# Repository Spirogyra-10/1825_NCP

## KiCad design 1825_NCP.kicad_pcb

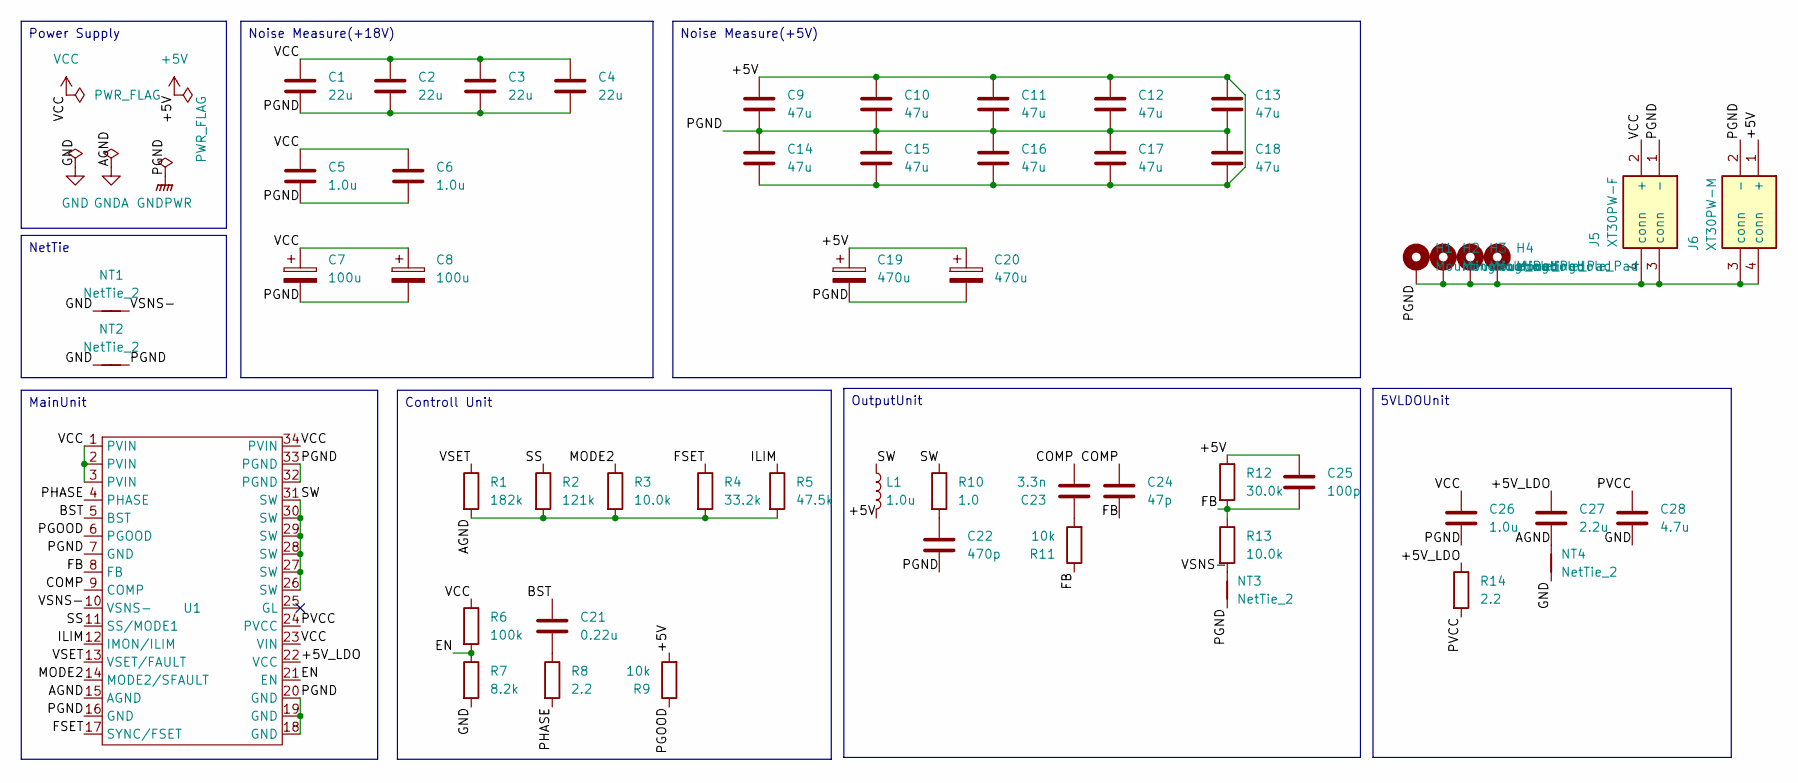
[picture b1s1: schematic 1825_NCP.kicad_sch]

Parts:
C1, C2, C3, C4: 22u; C_1210_3225Metric
C5, C6: 1.0u; C_0603_1608Metric
C7, C8: 100u; CP_Elec_8x10
C9, C10, C11, C12, C13, C14, C15, C16, C17, C18: 47u; C_1206_3216Metric
C19, C20: 470u; CP_EIA-7343-31_Kemet-D
C21: 0.22u; C_0603_1608Metric
C22: 470p; C_0805_2012Metric
C23: 3.3n; C_0603_1608Metric
C24: 47p; C_0603_1608Metric
C25: 100p; C_0603_1608Metric
C26: 1.0u; C_0805_2012Metric
C27: 2.2u; C_0603_1608Metric
C28: 4.7u; C_0805_2012Metric
H1, H2, H3, H4: MountingHole_Pad; MountingHole_3.2mm_M3_Pad_Via
J5: XT30PW-F; XT30PWF; Manufacturer_Part_Number XT30PW-F
J6: XT30PW-M; XT30PWM; Manufacturer_Part_Number XT30PW-M
L1: 1.0u; Pulse_PA4343
NT1, NT2, NT3, NT4: NetTie_2; NetTie-2_SMD_Pad0.5mm
R1: 182k; R_0603_1608Metric
R2: 121k; R_0603_1608Metric
R3, R13: 10.0k; R_0603_1608Metric
R4: 33.2k; R_0603_1608Metric
R5: 47.5k; R_0603_1608Metric
R6: 100k; R_0603_1608Metric
R7: 8.2k; R_0603_1608Metric
R8, R14: 2.2; R_0603_1608Metric
R9, R11: 10k; R_0603_1608Metric
R10: 1.0; R_1206_3216Metric
R12: 30.0k; R_0603_1608Metric
U1: NCP3294

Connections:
+5V: C9.1, C10.1, C11.1, C12.1, C13.1, C14.2, C15.2, C16.2, C17.2, C18.2, C19.1, C20.1, C25.1, J6.1 (+), L1.2, R9.2, R12.1
/+5V_LDO: C27.1, R14.1, U1.22 (VCC)
/BST: C21.1, U1.5 (BST)
/COMP: C23.2, C24.1, U1.9 (COMP)
/EN: R6.2, R7.1, U1.21 (EN)
/FB: C24.2, C25.2, R11.1, R12.2, R13.1, U1.8 (FB)
/FSET: R4.1, U1.17 (SYNC/FSET)
/ILIM: R5.1, U1.12 (IMON/ILIM)
/MODE2: R3.1, U1.14 (MODE2/SFAULT)
/PGOOD: R9.1, U1.6 (PGOOD)
/PHASE: R8.2, U1.4 (PHASE)
/PVCC: C28.1, R14.2, U1.24 (PVCC)
/SS: R2.1, U1.11 (SS/MODE1)
/SW: L1.1, R10.1, U1.26 (SW), U1.27 (SW), U1.28 (SW), U1.29 (SW), U1.30 (SW), U1.31 (SW)
/VSET: R1.1, U1.13 (VSET/FAULT)
/VSNS-: NT1.2, NT3.2, R13.2, U1.10 (VSNS-)
GND: C28.2, NT1.1, NT2.1, NT4.1, R7.2
GNDA: C27.2, NT4.2, R1.2, R2.2, R3.2, R4.2, R5.2, U1.15 (AGND)
GNDPWR: C1.2, C2.2, C3.2, C4.2, C5.2, C6.2, C7.2, C8.2, C9.2, C10.2, C11.2, C12.2, C13.2, C14.1, C15.1, C16.1, C17.1, C18.1, C19.2, C20.2, C22.2, C26.2, H1.1 (1_1), H2.1 (1_1), H3.1 (1_1), H4.1 (1_1), J5.1 (-), J5.3 (conn), J5.4 (conn), J6.2 (-), J6.3 (conn), J6.4 (conn), NT2.2, NT3.1, U1.7 (GND), U1.16 (GND), U1.18 (GND), U1.19 (GND), U1.20 (GND), U1.32 (PGND), U1.33 (PGND)
unnamed: C21.2, R8.1
unnamed: C22.1, R10.2
unnamed: C23.1, R11.2
VCC: C1.1, C2.1, C3.1, C4.1, C5.1, C6.1, C7.1, C8.1, C26.1, J5.2 (+), R6.1, U1.1 (PVIN), U1.2 (PVIN), U1.3 (PVIN), U1.23 (VIN), U1.34 (PVIN)

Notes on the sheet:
Power Supply
Controll Unit
Noise Measure(+5V)
MainUnit
OutputUnit
NetTie
5VLDOUnit
Noise Measure(+18V)

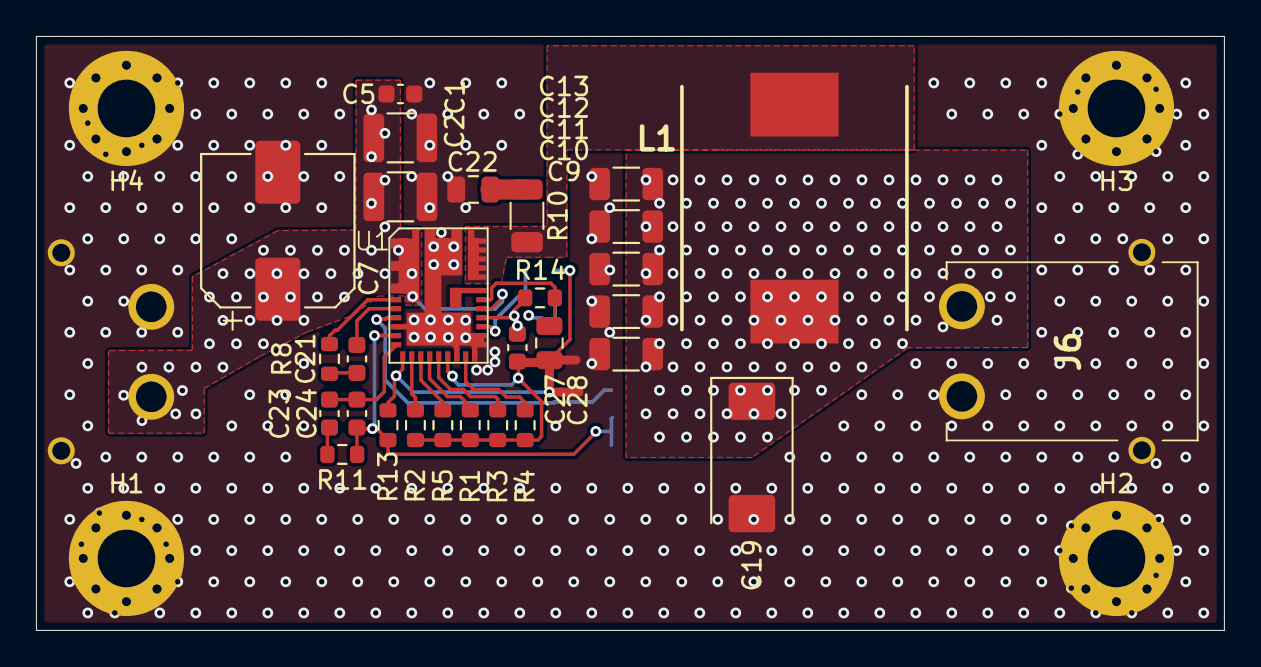
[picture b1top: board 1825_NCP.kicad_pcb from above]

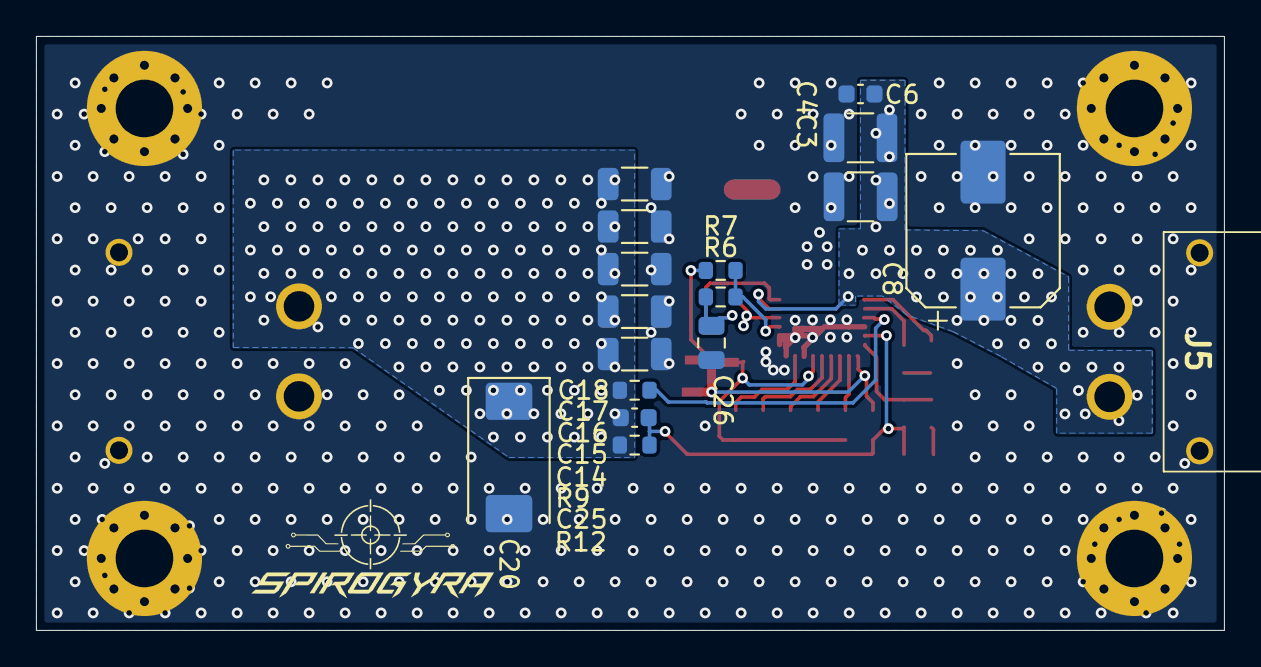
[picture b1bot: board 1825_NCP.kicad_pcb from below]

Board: 4 copper layers, 66.0 x 33.0 mm, 54 parts (17 on the bottom side), 23 nets.

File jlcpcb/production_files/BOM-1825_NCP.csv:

Comment,Designator,Footprint,LCSC,Quantity
2.2,R8,R_0603_1608Metric,,1
47p,C24,C_0603_1608Metric,,1
47u,C13,C_1206_3216Metric,,1
100u,C7,CP_Elec_8x10,,1
22u,C1,C_1210_3225Metric,,1
47u,C12,C_1206_3216Metric,,1
47u,C16,C_1206_3216Metric,,1
10.0k,R13,R_0603_1608Metric,,1
182k,R1,R_0603_1608Metric,,1
3.3n,C23,C_0603_1608Metric,,1
10.0k,R3,R_0603_1608Metric,,1
47u,C15,C_1206_3216Metric,,1
100k,R6,R_0603_1608Metric,,1
100p,C25,C_0603_1608Metric,,1
47u,C14,C_1206_3216Metric,,1
470u,C20,CP_EIA-7343-31_Kemet-D,,1
47.5k,R5,R_0603_1608Metric,,1
470p,C22,C_0805_2012Metric,,1
22u,C4,C_1210_3225Metric,,1
47u,C17,C_1206_3216Metric,,1
100u,C8,CP_Elec_8x10,,1
1.0u,C26,C_0805_2012Metric,,1
1.0u,C6,C_0603_1608Metric,,1
47u,C18,C_1206_3216Metric,,1
10k,R11,R_0603_1608Metric,,1
121k,R2,R_0603_1608Metric,,1
470u,C19,CP_EIA-7343-31_Kemet-D,,1
33.2k,R4,R_0603_1608Metric,,1
30.0k,R12,R_0603_1608Metric,,1
47u,C11,C_1206_3216Metric,,1
~,U1,NCP3294,,1
47u,C10,C_1206_3216Metric,,1
0.22u,C21,C_0603_1608Metric,,1
1.0,R10,R_1206_3216Metric,,1
1.0u,C5,C_0603_1608Metric,,1
2.2,R14,R_0603_1608Metric,,1
22u,C3,C_1210_3225Metric,,1
2.2u,C27,C_0603_1608Metric,,1
8.2k,R7,R_0603_1608Metric,,1
1.0u,L1,Pulse_PA4343,,1
22u,C2,C_1210_3225Metric,,1
47u,C9,C_1206_3216Metric,,1
10k,R9,R_0603_1608Metric,,1
4.7u,C28,C_0805_2012Metric,,1
XT30PW-M,J6,XT30PWM,,1
XT30PW-F,J5,XT30PWF,,1
